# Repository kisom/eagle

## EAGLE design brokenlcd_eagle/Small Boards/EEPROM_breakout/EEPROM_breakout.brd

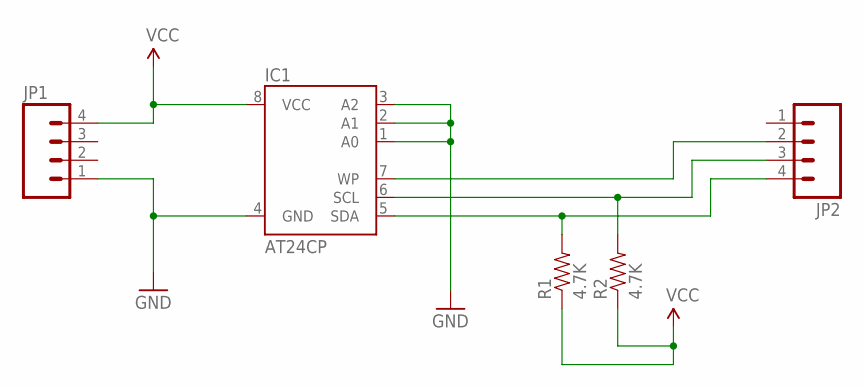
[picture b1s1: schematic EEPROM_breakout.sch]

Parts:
IC1: AT24CP; DIL08
JP1, JP2: M04LOCK; 1X04_LOCK
R1, R2: 4.7K; AXIAL-0.4

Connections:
GND: IC1.1 (A0), IC1.2 (A1), IC1.3 (A2), IC1.4 (GND), JP1.1
unnamed: IC1.5 (SDA), JP2.4, R1.P$2 (2)
unnamed: IC1.6 (SCL), JP2.3, R2.P$2 (2)
unnamed: IC1.7 (WP), JP2.2
VCC: IC1.8 (VCC), JP1.4, R1.P$1 (1), R2.P$1 (1)

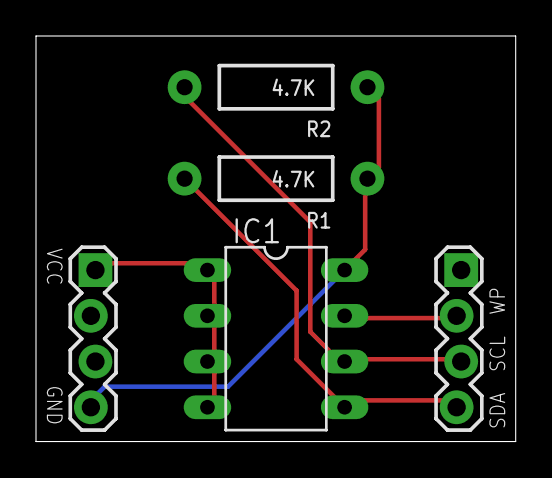
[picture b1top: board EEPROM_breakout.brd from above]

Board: 2 copper layers, 26.6 x 22.5 mm, 5 parts (0 on the bottom side), 5 nets.

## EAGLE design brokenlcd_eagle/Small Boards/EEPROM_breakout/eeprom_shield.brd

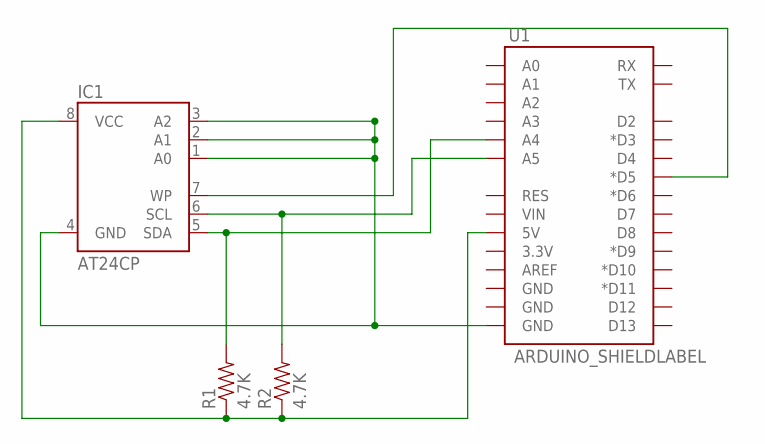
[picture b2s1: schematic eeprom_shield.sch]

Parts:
IC1: AT24CP; DIL08
R1, R2: 4.7K; AXIAL-0.4
U1: ARDUINO_SHIELDLABEL; DUEMILANOVE_SHIELD

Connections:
unnamed: IC1.1 (A0), IC1.2 (A1), IC1.3 (A2), IC1.4 (GND), U1.GND@0 (GND)
unnamed: IC1.6 (SCL), R2.P$2 (2), U1.A5
unnamed: IC1.7 (WP), U1.D5 (*D5)
unnamed: IC1.8 (VCC), R1.P$1 (1), R2.P$1 (1), U1.5V
unnamed: IC1.5 (SDA), R1.P$2 (2), U1.A4

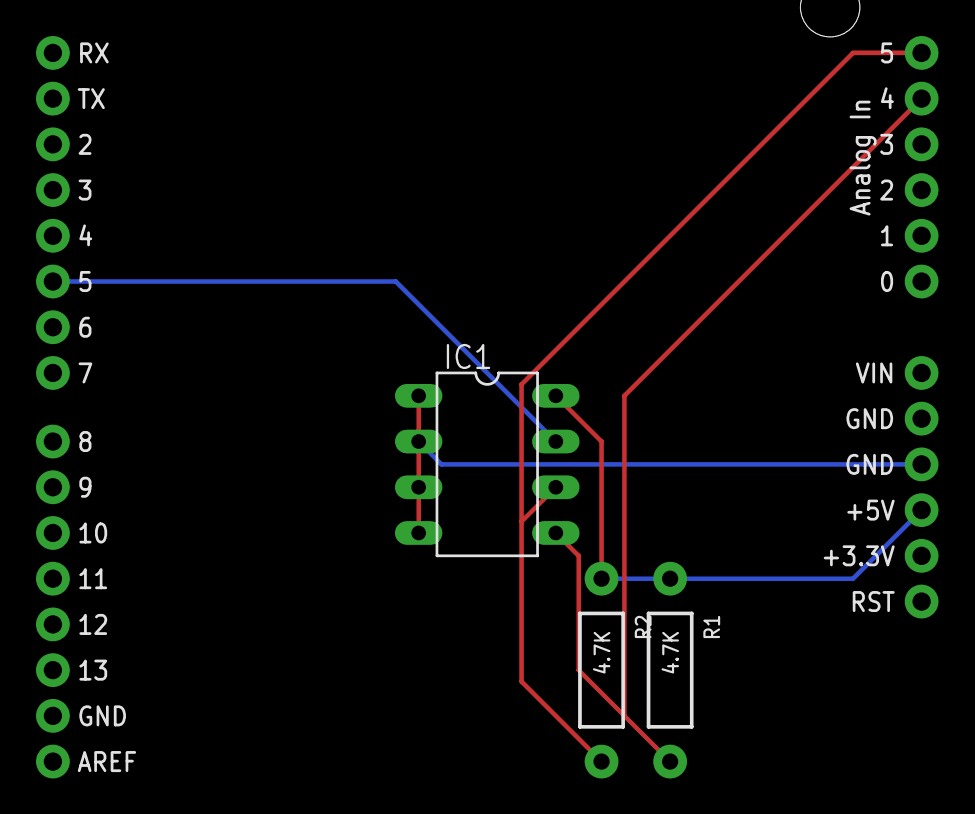
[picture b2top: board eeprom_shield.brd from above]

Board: 2 copper layers, 4 parts (0 on the bottom side), 5 nets.

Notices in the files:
parts and their libraries:
SparkFun-Connectors: Licensing: CC v3.0 Share-Alike You are welcome to use this library for commercial purposes.
